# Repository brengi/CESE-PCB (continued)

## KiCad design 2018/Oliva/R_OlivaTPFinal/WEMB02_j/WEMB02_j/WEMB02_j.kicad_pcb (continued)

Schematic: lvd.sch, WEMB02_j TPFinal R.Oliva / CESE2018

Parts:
C401: 0.1uF 50V; C_0805_2012Metric_Pad1.15x1.40mm_HandSolder
C402: 10uF 50V; EEE-1EA100WR
CR401: SMAJ15A; SMAJ70A
FR401: 0.25 A; C_Disc_D10.0mm_W2.5mm_P5.00mm
JP401: 48V; PinHeader_1x02_P2.54mm_Vertical
JP402: 24V; PinHeader_1x02_P2.54mm_Vertical
JP403: 12V; PinHeader_1x02_P2.54mm_Vertical
Q401: MMBTA42LT1G; SOT-23-3; MPN MMBTA42LT1G; Digi-Key_PN MMBTA42LT1GOSCT-ND
R401, R402, R406, R407: 10K; R_0805_2012Metric_Pad1.15x1.40mm_HandSolder
R403: 150K; R_0805_2012Metric_Pad1.15x1.40mm_HandSolder
R404: 56K; R_0805_2012Metric_Pad1.15x1.40mm_HandSolder
R405: 47K; R_0805_2012Metric_Pad1.15x1.40mm_HandSolder
RV401, RV402: 100 K MT; PV36W103C01B00
RV403, RV404: 10 K MT; PV36W103C01B00
TP401, TP402: TP1; TestPoint_Pad_D2.0mm
TP403, TP404, TP405: TP2; TestPoint_Pad_D2.0mm
U401: ICL7665ACSA+; ICL7665ACSA&plus_

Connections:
+BATT: FR401.2; also elsewhere on the board
/LowV_Detect/+B_LVD: C401.1, C402.1, CR401.1, JP403.2, Q401.2, R406.1, R407.1, RV403.1, RV403.2, RV404.1, RV404.2, TP405.1, U401.8
/LowV_Detect/-FEED_SHDN: R406.2, U401.1; also elsewhere on the board
/Power/SDM1: R407.2, U401.7; also elsewhere on the board
Earth: C401.2, C402.2, CR401.2, R401.2, R402.2, R405.2, U401.4; also elsewhere on the board
unnamed: FR401.1, JP401.1, JP402.1, JP403.1, Q401.3
unnamed: JP401.2, R403.1
unnamed: JP402.2, R404.1
unnamed: Q401.1, R403.2, R404.2, R405.1
unnamed: R401.1, RV401.1, TP401.1, U401.3
unnamed: R402.1, RV402.1, TP402.1, U401.6
unnamed: RV401.2, RV401.3, RV403.3, TP403.1, U401.2
unnamed: RV402.2, RV402.3, RV404.3, TP404.1, U401.5

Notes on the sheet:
LOW VOLTAGE DETECTOR - ICL7665 OUT1, OUT2 PROGRAMMABLE (SEE INSTRUCTIONS)
15V TVS
LOW VOLTAGE DETECTOR (DETECTOR DE BAJA TENSIÓN)
LOW VOLTAGE DETECTOR CIRCUIT - ICL7665
ACTIVE VOLTAGE DIVIDER FOR 12,24 OR 48 V SYSTEMS

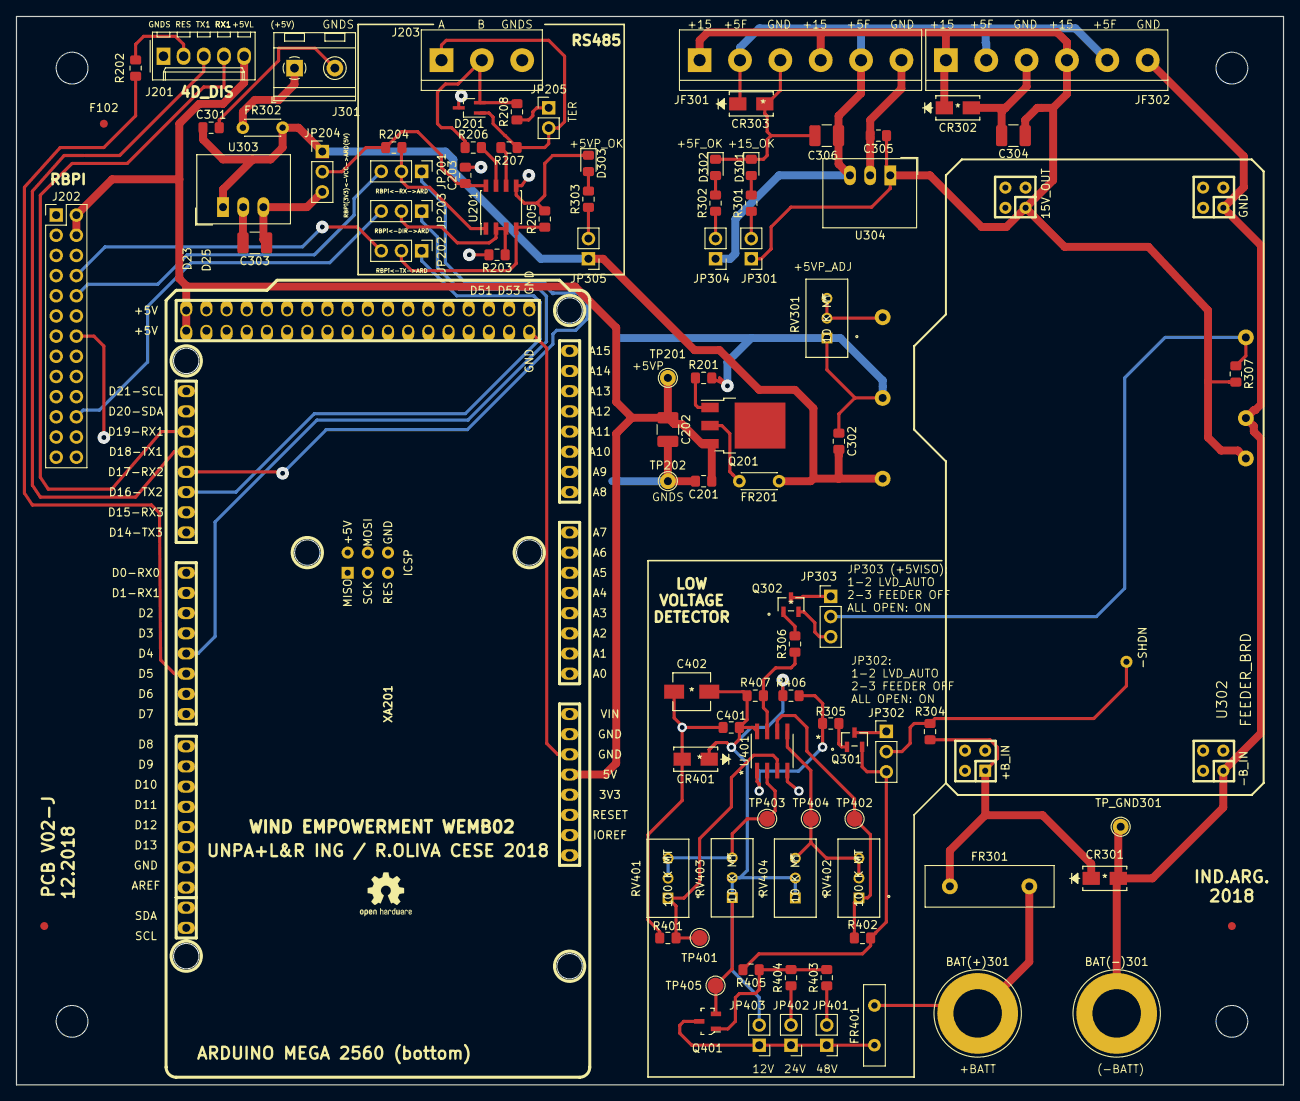
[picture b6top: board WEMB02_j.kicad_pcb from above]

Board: 2 copper layers, 159.5 x 134.5 mm, 97 parts (1 on the bottom side), 55 nets.
